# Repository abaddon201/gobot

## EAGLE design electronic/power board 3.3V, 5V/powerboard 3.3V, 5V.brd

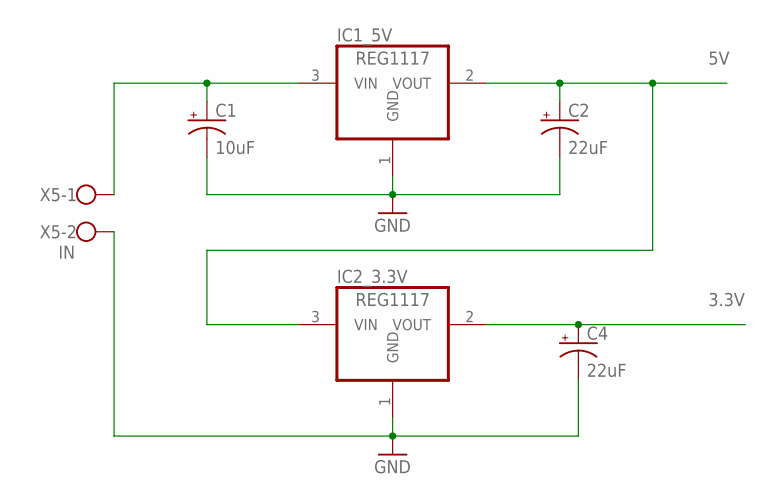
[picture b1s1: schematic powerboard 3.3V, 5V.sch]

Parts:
C1: 10uF; EIA3216
C2, C4: 22uF; EIA3528
IC1_5V, IC2_3.3V: REG1117; SOT223
X5: IN; W237-102

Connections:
3.3V: C4.A (+), IC2_3.3V.2 (VOUT)
5V: C2.A (+), IC1_5V.2 (VOUT), IC2_3.3V.3 (VIN)
GND: C1.-, C2.C (-), C4.C (-), IC1_5V.1 (GND), IC2_3.3V.1 (GND), X5.2
VIN: C1.+, IC1_5V.3 (VIN), X5.1

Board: 2 copper layers, 6 parts (0 on the bottom side), 4 nets, no tracks yet.

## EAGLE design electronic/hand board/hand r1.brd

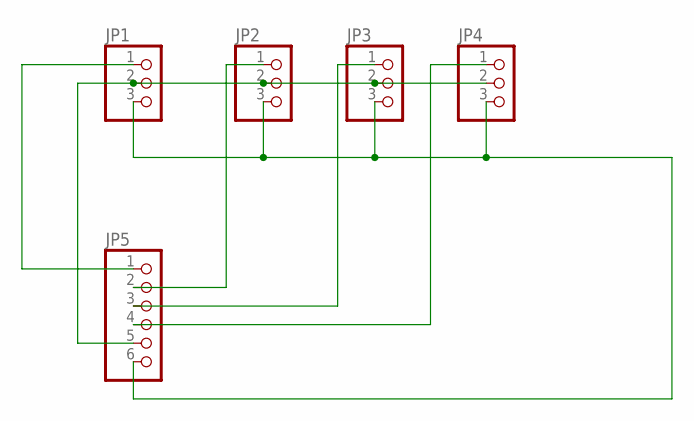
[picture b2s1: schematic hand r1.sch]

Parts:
JP1, JP2, JP3, JP4: PINHD-1X3; 1X03
JP5: PINHD-1X6; 1X06

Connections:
unnamed: JP1.3, JP2.3, JP3.3, JP4.3, JP5.6
unnamed: JP1.2, JP2.2, JP3.2, JP4.2, JP5.5
unnamed: JP4.1, JP5.4
unnamed: JP3.1, JP5.3
unnamed: JP2.1, JP5.2
unnamed: JP1.1, JP5.1

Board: 2 copper layers, 5 parts (0 on the bottom side), 6 nets, no tracks yet.

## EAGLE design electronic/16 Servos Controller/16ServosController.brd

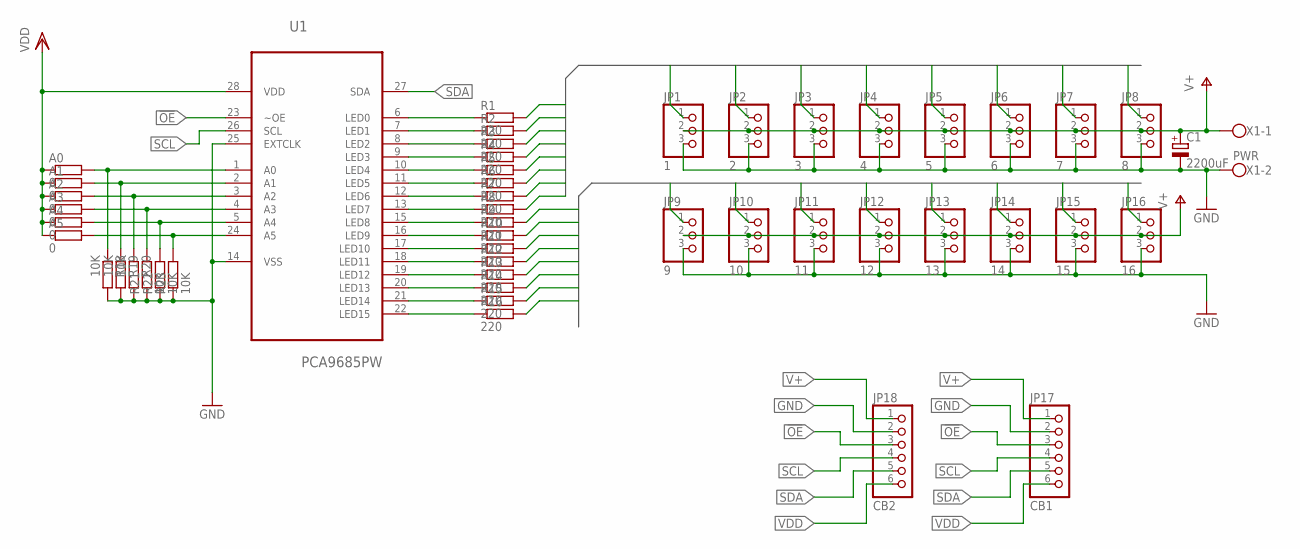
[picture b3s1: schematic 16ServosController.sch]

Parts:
A0, A1, A2, A3, A4, A5: 0; R0805
C1: 2200uF; E5-6
JP1: 1; 1X03
JP2: 2; 1X03
JP3: 3; 1X03
JP4: 4; 1X03
JP5: 5; 1X03
JP6: 6; 1X03
JP7: 7; 1X03
JP8: 8; 1X03
JP9: 9; 1X03
JP10: 10; 1X03
JP11: 11; 1X03
JP12: 12; 1X03
JP13: 13; 1X03
JP14: 14; 1X03
JP15: 15; 1X03
JP16: 16; 1X03
JP17: CB1; 1X06
JP18: CB2; 1X06
R1, R2, R3, R4, R5, R6, R7, R8, R9, R10, R11, R12, R13, R14, R15, R16: 220; R0805
R18, R19, R20, R21, R22, R23: 10K; R0805
U1: PCA9685PW; SOP65P640X110-28N
X1: PWR; W237-102

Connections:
!OE: JP17.3, JP18.3, U1.23 (~OE)
A0: A0.2, R18.1, U1.1 (A0)
A1: A1.2, R19.1, U1.2 (A1)
A2: A2.2, R20.1, U1.3 (A2)
A3: A3.2, R21.2, U1.4 (A3)
A4: A4.2, R22.2, U1.5 (A4)
A5: A5.2, R23.2, U1.24 (A5)
GND: C1.-, JP1.3, JP2.3, JP3.3, JP4.3, JP5.3, JP6.3, JP7.3, JP8.3, JP9.3, JP10.3, JP11.3, JP12.3, JP13.3, JP14.3, JP15.3, JP16.3, JP17.2, JP18.2, R18.2, R19.2, R20.2, R21.1, R22.1, R23.1, U1.14 (VSS), U1.25 (EXTCLK), X1.2
unnamed: R16.1, U1.22 (LED15)
unnamed: R1.1, U1.6 (LED0)
unnamed: R2.1, U1.7 (LED1)
unnamed: R3.1, U1.8 (LED2)
unnamed: R4.1, U1.9 (LED3)
unnamed: R5.1, U1.10 (LED4)
unnamed: R6.1, U1.11 (LED5)
unnamed: R7.1, U1.12 (LED6)
unnamed: R8.1, U1.13 (LED7)
unnamed: R9.1, U1.15 (LED8)
unnamed: R10.1, U1.16 (LED9)
unnamed: R11.1, U1.17 (LED10)
unnamed: R12.1, U1.18 (LED11)
unnamed: R13.1, U1.19 (LED12)
unnamed: R14.1, U1.20 (LED13)
unnamed: R15.1, U1.21 (LED14)
PWM1: JP1.1, R1.2
PWM2: JP2.1, R2.2
PWM3: JP3.1, R3.2
PWM4: JP4.1, R4.2
PWM5: JP5.1, R5.2
PWM6: JP6.1, R6.2
PWM7: JP7.1, R7.2
PWM8: JP8.1, R8.2
PWM9: JP9.1, R9.2
PWM10: JP10.1, R10.2
PWM11: JP11.1, R11.2
PWM12: JP12.1, R12.2
PWM13: JP13.1, R13.2
PWM14: JP14.1, R14.2
PWM15: JP15.1, R15.2
PWM16: JP16.1, R16.2
SCL: JP17.4, JP18.4, U1.26 (SCL)
SDA: JP17.5, JP18.5, U1.27 (SDA)
V+: C1.+, JP1.2, JP2.2, JP3.2, JP4.2, JP5.2, JP6.2, JP7.2, JP8.2, JP9.2, JP10.2, JP11.2, JP12.2, JP13.2, JP14.2, JP15.2, JP16.2, JP17.1, JP18.1, X1.1
VDD: A0.1, A1.1, A2.1, A3.1, A4.1, A5.1, JP17.6, JP18.6, U1.28 (VDD)

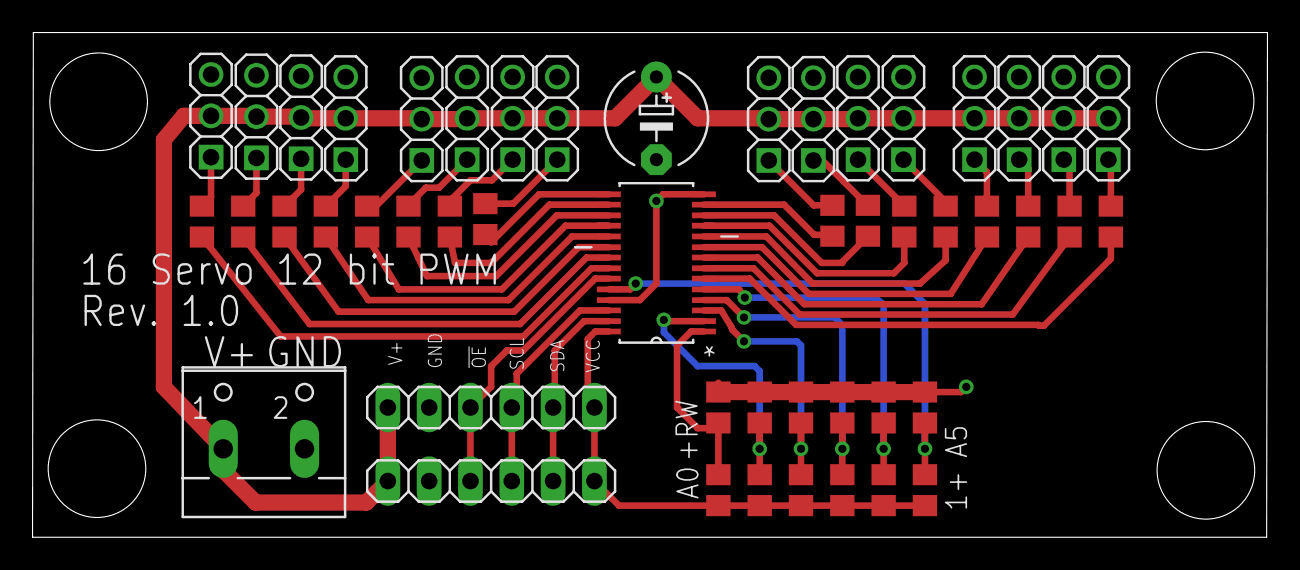
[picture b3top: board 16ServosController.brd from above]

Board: 2 copper layers, 75.9 x 31.0 mm, 49 parts (0 on the bottom side), 44 nets.

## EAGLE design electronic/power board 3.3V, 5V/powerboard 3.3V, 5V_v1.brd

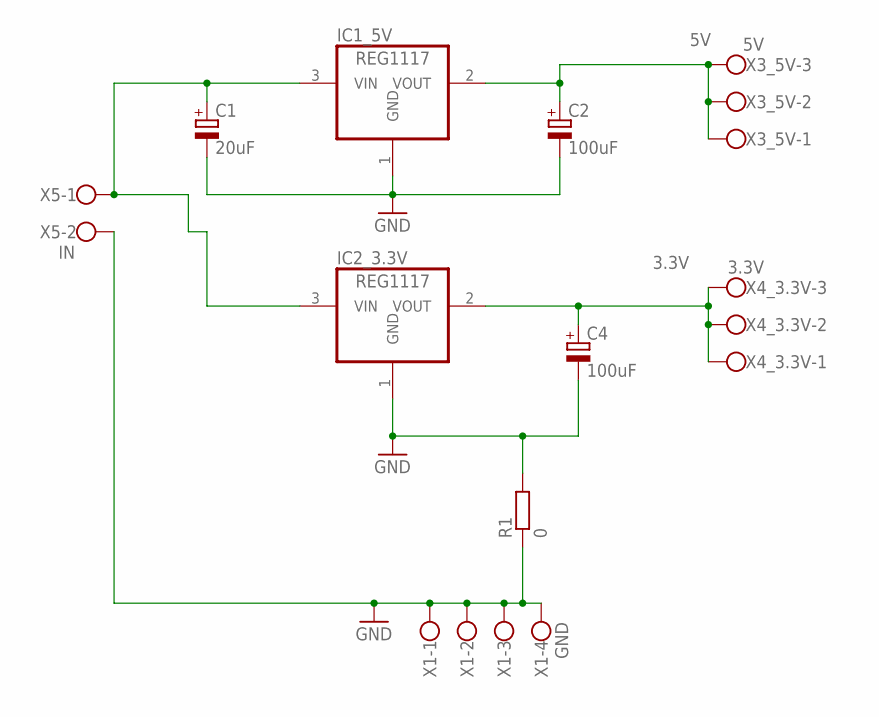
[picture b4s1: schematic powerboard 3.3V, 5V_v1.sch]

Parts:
C1: 20uF; E3,5-8
C2, C4: 100uF; E3,5-8
IC1_5V, IC2_3.3V: REG1117; SOT223
R1: 0; 0204/5
X1: GND; W237-4
X3_5V: 5V; W237-103
X4_3.3V: 3.3V; W237-103
X5: IN; W237-102

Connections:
3.3V: C4.+, IC2_3.3V.2 (VOUT), X4_3.3V.1, X4_3.3V.2, X4_3.3V.3
5V: C2.+, IC1_5V.2 (VOUT), X3_5V.1, X3_5V.2, X3_5V.3
GND: C1.-, C2.-, C4.-, IC1_5V.1 (GND), IC2_3.3V.1 (GND), R1.1, R1.2, X1.1, X1.2, X1.3, X1.4, X5.2
VIN: C1.+, IC1_5V.3 (VIN), IC2_3.3V.3 (VIN), X5.1

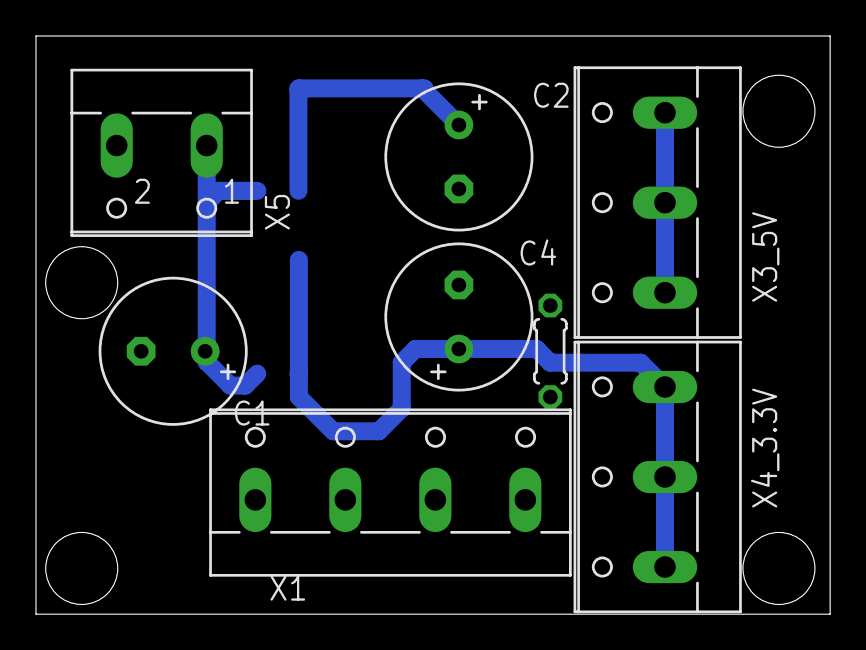
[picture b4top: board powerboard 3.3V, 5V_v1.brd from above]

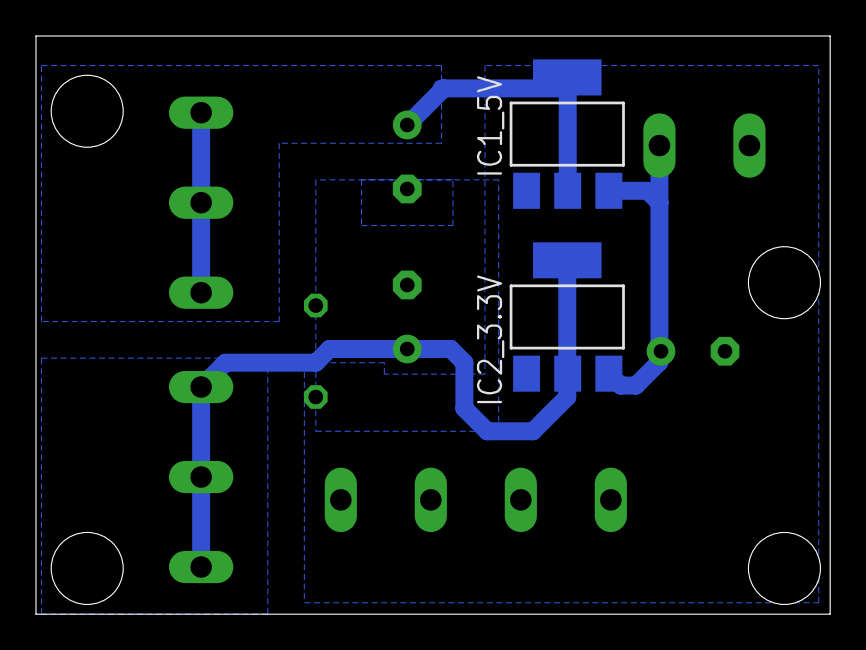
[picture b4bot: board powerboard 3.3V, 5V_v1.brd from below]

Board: 2 copper layers, 44.1 x 32.1 mm, 10 parts (2 on the bottom side), 4 nets.

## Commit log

2016-05-11 added power board for 3.3V and 5V converted from LiPo 2S or upper battery
2016-05-27 16 servo controller board. PWM 12 bits. Rev. 1.0
2016-05-30 ignores
2016-05-30 added chasis base plate
2016-05-30 added control sources
2016-05-30 added comments about connection pins to L298N big
2018-10-25 added hand board
2019-10-20 moved schematics to the KiCad
2019-11-21 scheme update

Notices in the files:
parts and their libraries:
SparkFun-Capacitors: Licensing: Creative Commons ShareAlike 4.0 International - https://creativecommons.org/licenses/by-sa/4.0
